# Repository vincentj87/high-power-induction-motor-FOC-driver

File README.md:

# High Power BLDC Motor Driver with Field-Oriented Control (FOC)
This repository contains an ongoing project for a high-power BLDC motor driver, capable of handling up to 92V. The motor driver implements the **Field-Oriented Control (FOC)** commutation method for enhanced efficiency. Additionally, it integrates **Maximum Torque Per Amp (MTPA)** control to optimize performance.

## Key Features:
- **Field-Oriented Control (FOC)**: For efficient commutation, reducing power losses and improving motor performance.
- **MTPA (Maximum Torque Per Amp)**: Optimizes motor operation for maximum torque output with minimal current draw.
- **High Power Handling**: Supports up to 92V for heavy-duty applications.
  
## Components:
All components included in the Bill of Materials (BOM) file are readily available through **LCSC** for easy sourcing.

## PCB Design:
- The controller PCB is designed for a **2-layer FR4** board.
- The MOSFET array is implemented on a **1-layer aluminum PCB** to maximize heat dissipation, particularly under heavy load conditions.

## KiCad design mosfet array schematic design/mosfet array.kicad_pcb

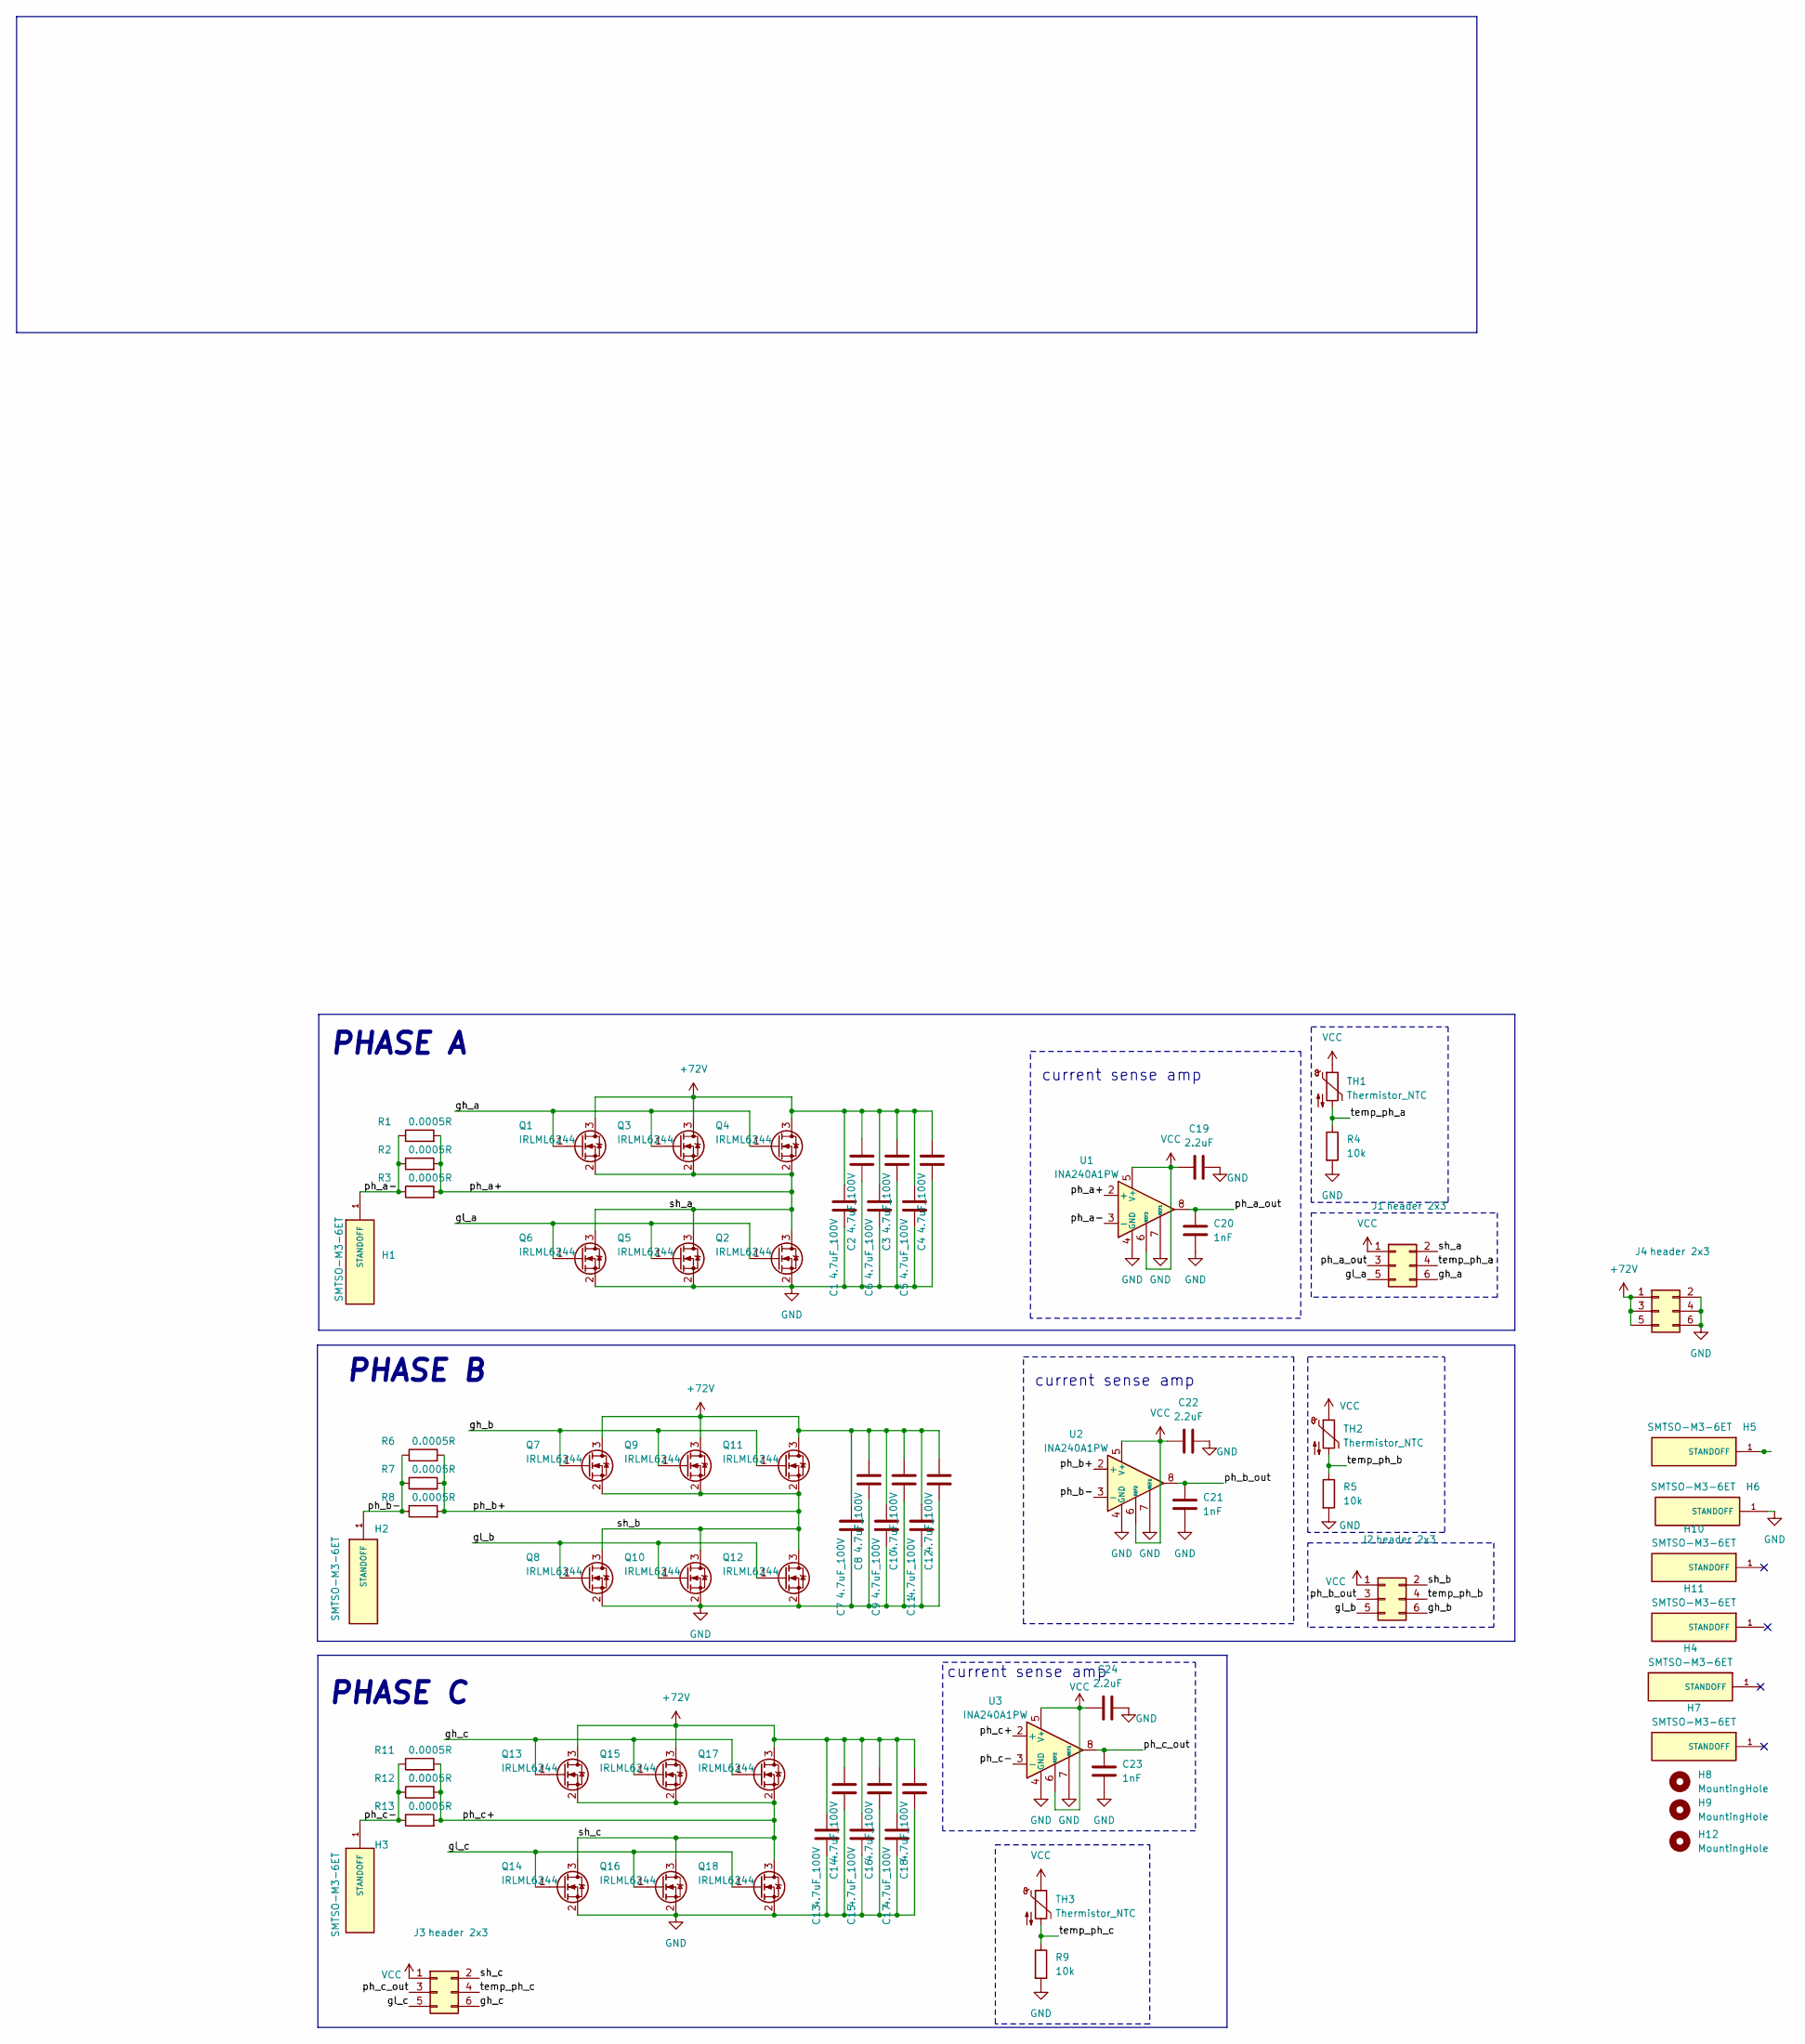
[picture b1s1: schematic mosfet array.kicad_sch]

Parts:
C1, C2, C3, C4, C5, C6, C7, C8, C9, C10, C11, C12, C13, C14, C15, C16, C17, C18: 4.7uF_100V; C_1210_3225Metric_Pad1.33x2.70mm_HandSolder; LCSC C697607
C19, C22, C24: 2.2uF; C_0402_1005Metric; LCSC C2176814
C20, C21, C23: 1nF; C_0402_1005Metric; LCSC C106205
H1, H2, H3, H5, H6: SMTSO-M3-6ET; PEM_SMTSO-M3-6ET; PARTREV 11/27/23; LCSC C30182787
H4, H7, H10, H11: SMTSO-M3-6ET; PEM_SMTSO-M3-6ET; PARTREV 11/27/23; LCSC C2916370
H8, H9, H12: MountingHole; MountingHole_3.2mm_M3
J1, J2, J3, J4: header 2x3; PinHeader_2x03_P2.54mm_Vertical_SMD; LCSC C192301
Q1, Q2, Q3, Q4, Q5, Q6, Q7, Q8, Q9, Q10, Q11, Q12, Q13, Q14, Q15, Q16, Q17, Q18: IRLML6244; Infineon_PG-HSOF-8-1; LCSC C697607
R1, R2, R3, R6, R7, R8, R11, R12, R13: 0.0005R; R_2512_6332Metric; LCSC C5119469
R4, R5, R9: 10k; R_0402_1005Metric; LCSC C60490
TH1, TH2, TH3: Thermistor_NTC; R_0402_1005Metric; LCSC C2689808
U1, U2, U3: INA240A1PW; TSSOP-8_4.4x3mm_P0.65mm; LCSC C93965

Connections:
+72V: C1.1, C2.1, C3.1, C4.1, C5.1, C6.1, C7.1, C8.1, C9.1, C10.1, C11.1, C12.1, C13.1, C14.1, C15.1, C16.1, C17.1, C18.1, J4.1, J4.3, J4.5, Q1.3 (D), Q3.3 (D), Q4.3 (D), Q7.3 (D), Q9.3 (D), Q11.3 (D), Q13.3 (D), Q15.3 (D), Q17.3 (D)
/gh_a: J1.6, Q1.1 (G), Q3.1 (G), Q4.1 (G)
/gh_b: J2.6, Q7.1 (G), Q9.1 (G), Q11.1 (G)
/gh_c: J3.6, Q13.1 (G), Q15.1 (G), Q17.1 (G)
/gl_a: J1.5, Q2.1 (G), Q5.1 (G), Q6.1 (G)
/gl_b: J2.5, Q8.1 (G), Q10.1 (G), Q12.1 (G)
/gl_c: J3.5, Q14.1 (G), Q16.1 (G), Q18.1 (G)
/ph_a+: J1.2, Q1.2 (S), Q2.3 (D), Q3.2 (S), Q4.2 (S), Q5.3 (D), Q6.3 (D), R1.2, R2.2, R3.2, U1.2 (+)
/ph_a-: H1.1 (STANDOFF), R1.1, R2.1, R3.1, U1.3 (-)
/ph_a_out: C20.2, J1.3, U1.8
/ph_b+: J2.2, Q7.2 (S), Q8.3 (D), Q9.2 (S), Q10.3 (D), Q11.2 (S), Q12.3 (D), R6.2, R7.2, R8.2, U2.2 (+)
/ph_b-: H2.1 (STANDOFF), R6.1, R7.1, R8.1, U2.3 (-)
/ph_b_out: C21.2, J2.3, U2.8
/ph_c+: J3.2, Q13.2 (S), Q14.3 (D), Q15.2 (S), Q16.3 (D), Q17.2 (S), Q18.3 (D), R11.2, R12.2, R13.2, U3.2 (+)
/ph_c-: H3.1 (STANDOFF), R11.1, R12.1, R13.1, U3.3 (-)
/ph_c_out: C23.2, J3.3, U3.8
/temp_ph_a: J1.4, R4.1, TH1.2
/temp_ph_b: J2.4, R5.1, TH2.2
/temp_ph_c: J3.4, R9.1, TH3.2
GND: C1.2, C2.2, C3.2, C4.2, C5.2, C6.2, C7.2, C8.2, C9.2, C10.2, C11.2, C12.2, C13.2, C14.2, C15.2, C16.2, C17.2, C18.2, C19.2, C20.1, C21.1, C22.2, C23.1, C24.2, H6.1 (STANDOFF), J4.2, J4.4, J4.6, Q2.2 (S), Q5.2 (S), Q6.2 (S), Q8.2 (S), Q10.2 (S), Q12.2 (S), Q14.2 (S), Q16.2 (S), Q18.2 (S), R4.2, R5.2, R9.2, U1.1 (GND), U1.4 (GND), U1.7 (REF1), U2.1 (GND), U2.4 (GND), U2.7 (REF1), U3.1 (GND), U3.4 (GND), U3.7 (REF1)
VCC: C19.1, C22.1, C24.1, J1.1, J2.1, J3.1, TH1.1, TH2.1, TH3.1, U1.5 (V+), U1.6 (REF2), U2.5 (V+), U2.6 (REF2), U3.5 (V+), U3.6 (REF2)

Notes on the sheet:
current sense amp
PHASE A
PHASE B
PHASE C

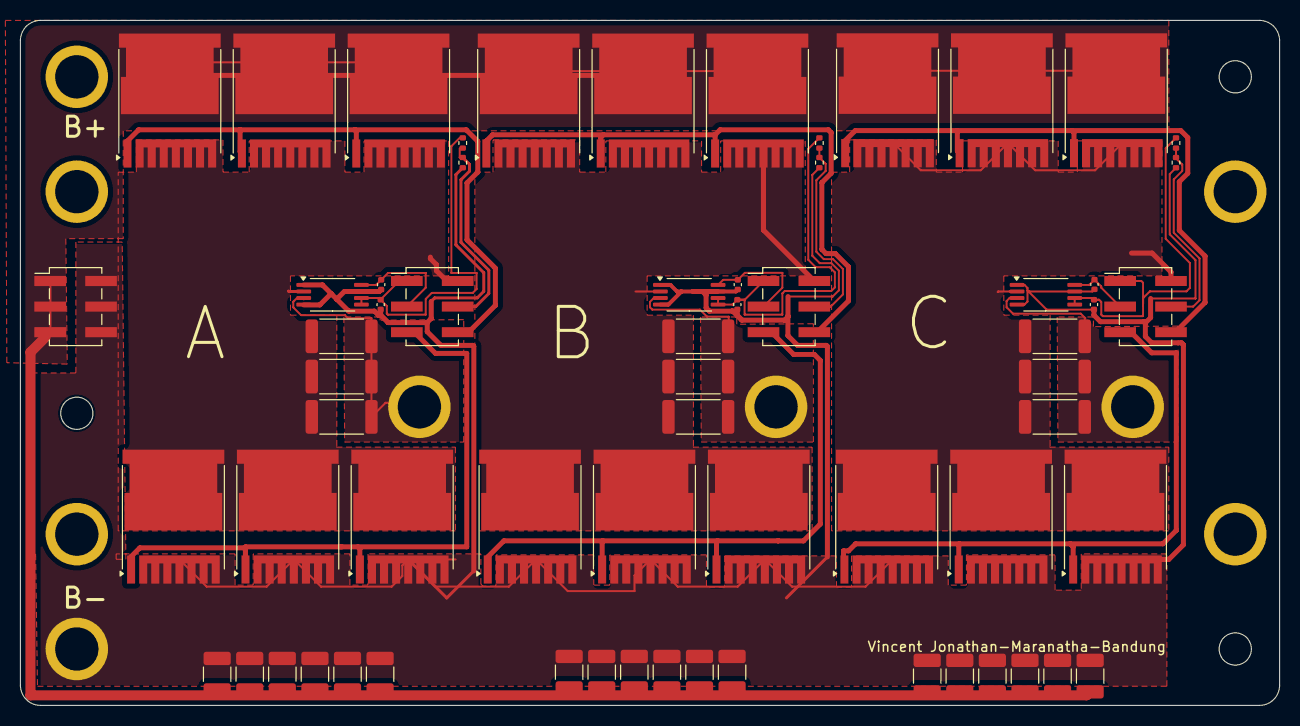
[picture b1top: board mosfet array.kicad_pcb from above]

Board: 2 copper layers, 125.0 x 68.0 mm, 76 parts (0 on the bottom side), 21 nets.

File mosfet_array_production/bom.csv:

Designator,Footprint,Quantity,Value,LCSC Part #
"C1, C10, C11, C12, C13, C14, C15, C16, C17, C18, C2, C3, C4, C5, C6, C7, C8, C9",1210,18,4.7uF_100V,C697607
"C19, C22, C24",0402,3,2.2uF,C2176814
"C20, C21, C23",0402,3,1nF,C106205
"H1, H2, H3, H5, H6",PEM_SMTSO-M3-6ET,5,SMTSO-M3-6ET,C30182787 
"H10, H11, H4, H7",PEM_SMTSO-M3-6ET,4,SMTSO-M3-6ET,C2916370 
"J1, J2, J3, J4",PinHeader_2x03_P2.54mm_Vertical_SMD,4,header 2x3,C192301 
"Q1, Q10, Q11, Q12, Q13, Q14, Q15, Q16, Q17, Q18, Q2, Q3, Q4, Q5, Q6, Q7, Q8, Q9",Infineon_PG-HSOF-8-1,18,IRLML6244,C697607
"R1, R11, R12, R13, R2, R3, R6, R7, R8",2512,9,0.0005R,C5119469
"R4, R5, R9",0402,3,10k,C60490
"TH1, TH2, TH3",0402,3,Thermistor_NTC,C2689808
"U1, U2, U3",TSSOP-8_4.4x3mm_P0.65mm,3,INA240A1PW,C93965

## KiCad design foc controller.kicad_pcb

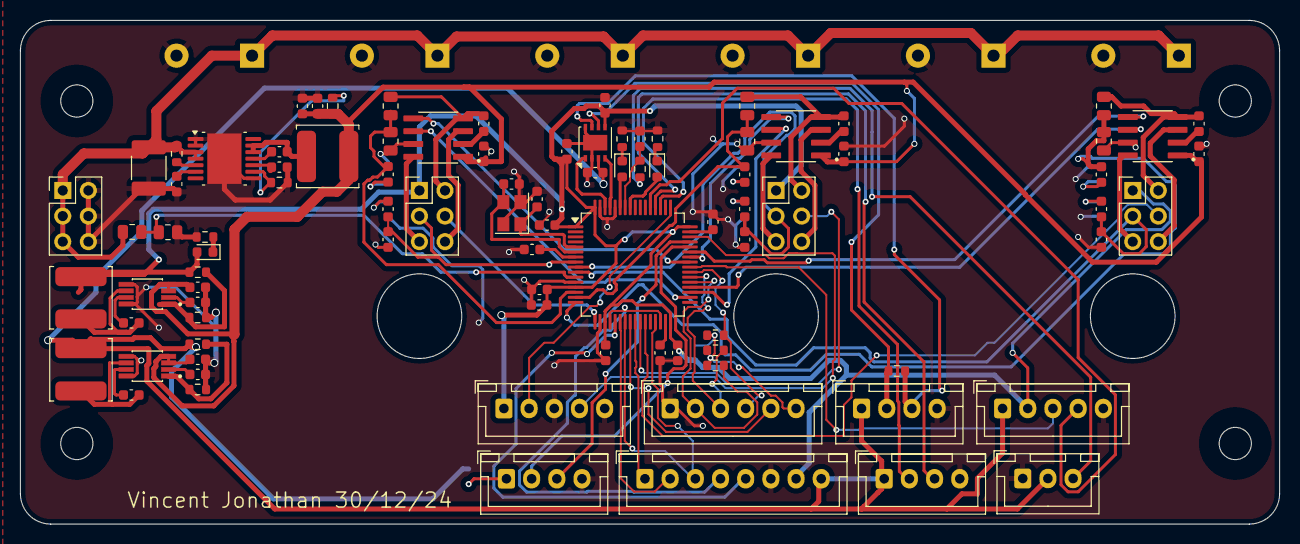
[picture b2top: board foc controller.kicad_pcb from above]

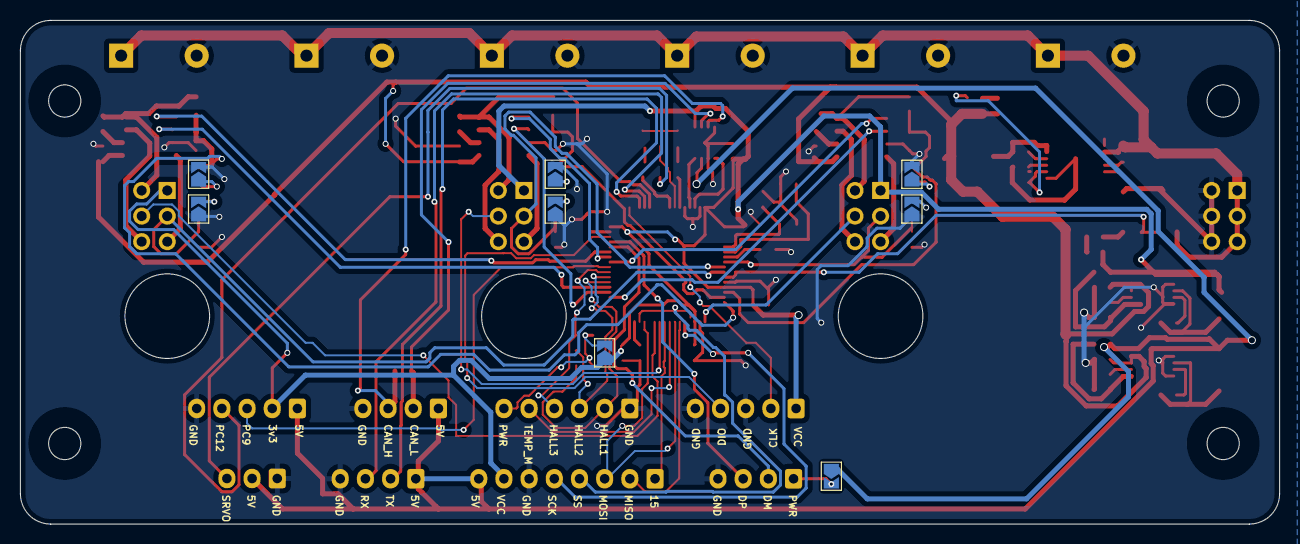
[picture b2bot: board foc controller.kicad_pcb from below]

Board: 2 copper layers, 125.0 x 50.0 mm, 109 parts (8 on the bottom side), 88 nets.

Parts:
C1, C2: 20pF; C_0603_1608Metric
C3, C4, C6, C7, C8, C9, C10, C11, C12, C15, C17, C20, C22, C25, C26, C27, C28: 2.2uf; C_0603_1608Metric
C5, C13, C14, C16, C21, C24, C29, C30, C31, C32, C41: 100nF; C_0603_1608Metric
C18: 10nF; C_0603_1608Metric
C19: 4.7uF 100V; C_1812_4532Metric
C23: 22uF_16V; C_0603_1608Metric
C33, C36, C38: 1nF; C_0603_1608Metric
C34, C35, C37: 15nF; C_0603_1608Metric
C39, C40: 2.2uF; C_0603_1608Metric
C42, C43, C44, C45, C46, C47: 470uF_100V; CP_Radial_D16.0mm_P7.50mm
D1, D2, D3: LED; LED_0603_1608Metric
H1, H2, H3, H4: MountingHole; MountingHole_3.2mm_M3
J1, J2, J3, J4: Conn_02x03_Odd_Even; PinHeader_2x03_P2.54mm_Vertical
J5, J6, J12: Conn_01x04; JST_XH_B4B-XH-A_1x04_P2.50mm_Vertical
J7: Conn_01x06; JST_XH_B6B-XH-A_1x06_P2.50mm_Vertical
J8: Conn_01x08; JST_XH_B8B-XH-A_1x08_P2.50mm_Vertical
J9: Conn_01x03; JST_XH_B3B-XH-A_1x03_P2.50mm_Vertical
J10, J11: Conn_01x05; JST_XH_B5B-XH-A_1x05_P2.50mm_Vertical
JP1, JP2, JP4, JP5, JP6, JP8: DNP; SolderJumper-2_P1.3mm_Open_TrianglePad1.0x1.5mm
JP3: Jumper_2_Open; SolderJumper-2_P1.3mm_Open_TrianglePad1.0x1.5mm
JP7: Jumper_3_Open; SolderJumper-2_P1.3mm_Open_TrianglePad1.0x1.5mm
L1, L2, L3: 100uH 1A; L_TDK_VLS6045EX_VLS6045AF
R1: 402k; R_0603_1608Metric
R2, R5, R7: 10k; R_0603_1608Metric
R3: 2k; R_0603_1608Metric
R4, R6: 33k; R_0603_1608Metric
R8, R10, R12, R14: 56k 0.5W; R_0805_2012Metric
R9, R11, R13, R15: 2.2k; R_0805_2012Metric
R16, R17, R18, R19: 220R; R_0603_1608Metric
R20, R21, R22: 2.2k; R_0603_1608Metric
R23: 100R; R_0603_1608Metric
U1: STM32F405RGTx; LQFP-64_10x10mm_P0.5mm
U2, U3, U4: UCC27210D; SOIC127P599X175-8N
U5: LM5161PWP; HTSSOP-14-1EP_4.4x5mm_P0.65mm_EP3.4x5mm_Mask3x3.1mm
U6, U7: MCP16311-E_MS; SOP65P490X110-8N
U8: TJA1051TK-3; DFN-8-1EP_3x3mm_P0.65mm_EP1.55x2.4mm
Y1: 8Mhz; Crystal_SMD_3225-4Pin_3.2x2.5mm

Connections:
+5V: C40.1, J5.1, J6.1, J8.8, J9.2, J11.1, JP3.1 (A), L3.2, R6.1, U8.3 (VCC)
+12V: C12.1, C15.1, C17.1, C22.1, C23.1, C25.1, C27.1, L1.2, R2.2, U2.1 (VDD), U3.1 (VDD), U4.1 (VDD), U6.3 (EN), U6.4 (VIN), U7.3 (EN), U7.4 (VIN)
+BATT: C19.1, C42.1, C43.1, C44.1, C45.1, C46.1, C47.1, J4.1, J4.3, J4.5, R1.1, R8.1, U5.3 (VIN), U5.4 (EN/UVLO)
/STM32F405/ADC_15: J8.1, U1.25 (PC5)
/STM32F405/ADC_TEMP: J1.4, U1.17 (PA3)
/STM32F405/ADC_TEMP2: J2.4, U1.26 (PB0)
/STM32F405/ADC_TEMP3: J3.4, U1.27 (PB1)
/STM32F405/AN_IN: R8.2, R9.1, U1.11 (PC3)
/STM32F405/CAN_RX: U1.61 (PB8), U8.4 (RXD)
/STM32F405/CAN_TX: U1.62 (PB9), U8.1 (TXD)
/STM32F405/CURRENT_1: C33.1, C34.1, J1.3, U1.8 (PC0)
/STM32F405/CURRENT_2: C35.1, C36.1, J2.3, U1.9 (PC1)
/STM32F405/CURRENT_3: C37.1, C38.1, J3.3, U1.10 (PC2)
/STM32F405/H1: U1.41 (PA8), U3.5 (HI)
/STM32F405/H2: U1.42 (PA9), U2.5 (HI)
/STM32F405/H3: U1.43 (PA10), U4.5 (HI)
/STM32F405/HALL_1: J7.2, R20.1, U1.37 (PC6)
/STM32F405/HALL_2: J7.3, R21.1, U1.38 (PC7)
/STM32F405/HALL_3: J7.4, R22.1, U1.39 (PC8)
/STM32F405/L1: U1.34 (PB13), U3.6 (LI)
/STM32F405/L2: U1.35 (PB14), U2.6 (LI)
/STM32F405/L3: U1.36 (PB15), U4.6 (LI)
/STM32F405/LED_GREEN: D2.2 (A), U1.57 (PB5)
/STM32F405/LED_RED: D1.2 (A), U1.59 (PB7)
/STM32F405/MISO_ADC_EXT2: J8.2, U1.22 (PA6)
/STM32F405/PC9: J11.3, U1.40 (PC9)
/STM32F405/PC10_UART_TX: J6.2, U1.51 (PC10)
/STM32F405/PC11_UART_RX: J6.3, U1.52 (PC11)
/STM32F405/PC12: J11.4, U1.53 (PC12)
/STM32F405/RX_SDA_NSS: J8.4, U1.20 (PA4), U1.30 (PB11)
/STM32F405/SCK_ADC_EXT: J8.5, U1.21 (PA5)
/STM32F405/SERVO: C41.2, R23.2, U1.58 (PB6)
/STM32F405/SWCLK: J10.2, U1.49 (PA14)
/STM32F405/SWDIO: J10.4, U1.46 (PA13)
/STM32F405/TEMP_MOTOR: J7.5, U1.24 (PC4)
/STM32F405/TX_SCL_MOSI: J8.3, U1.23 (PA7), U1.29 (PB10)
/STM32F405/USB_DM: J12.2, U1.44 (PA11)
/STM32F405/USB_DP: J12.3, U1.45 (PA12)
/STM32F405/VOLTAGE_1: C30.1, R10.2, R11.1, U1.14 (PA0)
/STM32F405/VOLTAGE_2: C31.1, R12.2, R13.1, U1.15 (PA1)
/STM32F405/VOLTAGE_3: C32.1, R14.2, R15.1, U1.16 (PA2)
/can bus/CAN_H: J5.3, R19.2, U8.7 (CANH)
/can bus/CAN_L: J5.2, R19.1, U8.6 (CANL)
/driver/HO1: J1.6, U3.3 (HO)
/driver/HO2: J2.6, U2.3 (HO)
/driver/HO3: J3.6, U4.3 (HO)
/driver/HS1: C13.2, J1.2, R10.1, U3.4 (HS)
/driver/HS2: C14.2, J2.2, R12.1, U2.4 (HS)
/driver/HS3: C16.2, J3.2, R14.1, U4.4 (HS)
/driver/LO1: J1.5, U3.8 (LO)
/driver/LO2: J2.5, U2.8 (LO)
/driver/LO3: J3.5, U4.8 (LO)
GND: C1.1, C2.1, C3.2, C4.2, C5.1, C6.1, C7.1, C8.2, C9.2, C10.2, C11.2, C12.2, C15.2, C17.2, C18.2, C19.2, C20.2, C22.2, C23.2, C25.2, C26.2, C27.2, C28.2, C33.2, C36.2, C38.2, C39.2, C40.2, C41.1, C42.2, C43.2, C44.2, C45.2, C46.2, C47.2, J4.2, J4.4, J4.6, J5.4, J6.4, J7.1, J8.6, J9.1, J10.3, J10.5, J11.5, J12.4, JP1.2 (B), JP2.2 (B), JP4.1 (A), JP5.1 (A), JP6.1 (A), JP8.2 (B), R3.1, R5.1, R7.1, R9.2, R11.2, R13.2, R15.2, R16.2, R17.2, R18.2, U1.12 (VSSA), U1.18 (VSS), U1.60 (BOOT0), U1.63 (VSS), U2.7 (VSS), U3.7 (VSS), U4.7 (VSS), U5.1 (AGND), U5.2 (PGND), U5.8 (FPWM), U5.15 (AGND), U6.5 (PGND), U6.8 (AGND), U7.5 (PGND), U7.8 (AGND), U8.2 (GND), U8.8 (S), U8.9 (GND), Y1.2, Y1.4
unnamed: C21.2, L1.1, U5.12 (SW), U5.13 (SW)
unnamed: D1.1 (K), R16.1
unnamed: D2.1 (K), R17.1
unnamed: D3.1 (K), R18.1
unnamed: J7.6, JP7.2 (C), R20.2, R21.2, R22.2
unnamed: J9.3, R23.1
unnamed: J12.1, JP3.2 (B)
unnamed: C30.2, JP1.1 (A)
unnamed: C31.2, JP2.1 (A)
unnamed: C34.2, JP4.2 (B)
unnamed: C35.2, JP5.2 (B)
unnamed: C37.2, JP6.2 (B)
unnamed: C32.2, JP8.1 (A)
unnamed: C5.2, U1.7 (NRST)
unnamed: C1.2, U1.5 (PH0), Y1.1
unnamed: C2.2, U1.6 (PH1), Y1.3
unnamed: C6.2, U1.31 (VCAP_1)
unnamed: C7.2, U1.47 (VCAP_2)
unnamed: C14.1, U2.2 (HB)
unnamed: C13.1, U3.2 (HB)
unnamed: C16.1, U4.2 (HB)
unnamed: C21.1, U5.11 (BST)
unnamed: R2.1, R3.2, U5.9 (FB)
unnamed: R1.2, U5.5 (RON)
unnamed: C18.1, U5.6 (SS)
unnamed: C20.1, U5.10 (VCC)
unnamed: C29.1, U6.7 (BOOST)
unnamed: C29.2, L3.1, U6.6 (SW)
unnamed: C28.1, U6.2 (VCC)
unnamed: R6.2, R7.2, U6.1 (VFB)
unnamed: C24.1, U7.7 (BOOST)
unnamed: C24.2, L2.1, U7.6 (SW)
unnamed: C26.1, U7.2 (VCC)
unnamed: R4.2, R5.2, U7.1 (VFB)
VCC: C3.1, C4.1, C8.1, C9.1, C10.1, C11.1, C39.1, D3.2 (A), J1.1, J2.1, J3.1, J8.7, J10.1, J11.2, JP7.1 (A), L2.2, R4.1, U1.1 (VBAT), U1.13 (VDDA), U1.19 (VDD), U1.32 (VDD), U1.48 (VDD), U1.64 (VDD), U8.5 (VIO)

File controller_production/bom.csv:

Designator,Footprint,Quantity,Value,LCSC Part #
"C1, C2",0603,2,20pF,C5137583
"C10, C11, C12, C15, C17, C20, C22, C25, C26, C27, C28, C3, C39, C4, C40, C8, C9",0603,17,2.2uf,C2835569
"C13, C14, C16, C21, C24, C29, C30, C31, C32, C41, C5",0603,11,100nF,C14663
C18,0603,1,10nF,C100042
C19,1812,1,4.7uF 100V,C2831628
C23,0603,1,22uF_16V,C59461
"C33, C36, C38",0603,3,1nF,C342905
"C34, C35, C37",0603,3,15nF,C527994
"C42, C43, C44, C45, C46, C47",CP_Radial_D16.0mm_P7.50mm,6,470uF_100V,C365811
"C6, C7",0603,2,2.2uf,C2167658
"D1, D3",0603,2,LED,C3291493
D2,0603,1,LED,C496821
"J1, J2, J3, J4",PinHeader_2x03_P2.54mm_Vertical,4,Conn_02x03_Odd_Even,C32713304
"J10, J11",JST_XH_B5B-XH-A_1x05_P2.50mm_Vertical,2,Conn_01x05,C157991
"J12, J5, J6",JST_XH_B4B-XH-A_1x04_P2.50mm_Vertical,3,Conn_01x04,C144395
J7,JST_XH_B6B-XH-A_1x06_P2.50mm_Vertical,1,Conn_01x06,C144397
J8,JST_XH_B8B-XH-A_1x08_P2.50mm_Vertical,1,Conn_01x08,C157972
J9,JST_XH_B3B-XH-A_1x03_P2.50mm_Vertical,1,Conn_01x03,C144394
JP1,SolderJumper-2_P1.3mm_Open_TrianglePad1.0x1.5mm,1,DNP,DNP
"JP2, JP4, JP5, JP6, JP8",SolderJumper-2_P1.3mm_Open_TrianglePad1.0x1.5mm,5,DNP,
JP3,SolderJumper-2_P1.3mm_Open_TrianglePad1.0x1.5mm,1,Jumper_2_Open,
"L1, L2, L3",L_TDK_VLS6045EX_VLS6045AF,3,100uH 1A,C2042037
R1,0603,1,402k,C705774
"R10, R12, R14, R8",0805,4,56k 0.5W,C441990
"R11, R13, R15, R9",0805,4,2.2k,C2078022
"R16, R17, R18, R19",0603,4,220R,C351666
"R2, R5, R7",0603,3,10k,C98220
"R20, R21, R22",0603,3,2.2k,C2078022
R23,0603,1,100R,C855560
R3,0603,1,2k,C103396
"R4, R6",0603,2,33k,C163907
U1,LQFP-64_10x10mm_P0.5mm,1,STM32F405RGTx,C15742
"U2, U3, U4",SOIC127P599X175-8N,3,UCC27210D,C2871979
U5,HTSSOP-14-1EP_4.4x5mm_P0.65mm_EP3.4x5mm_Mask3x3.1mm,1,LM5161PWP,C468246
"U6, U7",SOP65P490X110-8N,2,MCP16311-E_MS,C627024
U8,DFN-8-1EP_3x3mm_P0.65mm_EP1.55x2.4mm,1,TJA1051TK-3,C2875699
Y1,Crystal_SMD_3225-4Pin_3.2x2.5mm,1,8Mhz,C5265856

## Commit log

2025-01-02 Create test
2025-01-02 Create temp
